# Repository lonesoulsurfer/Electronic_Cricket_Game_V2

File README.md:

# Electronic Cricket Game V2

This is a handheld electronic cricket game. Score as many runs as possible before you are out. It is a good project to learn to solder.

## Build guide and video

- Step-by-step build guide on Instructables: [Electronic Cricket Game V2](https://www.instructables.com/Electronic-Cricket-Game-V2/)
- Video on YouTube: [Electronic Cricket Game](https://youtu.be/J4yHMKsFy00)

## How to play

- Score as many runs as possible before you are out.
- I usually allow 3 outs, then the game is over.
- The board shows some cricket words, to help you learn the game. The Instructables guide has a glossary and the full rules.

## What you need

- All parts are in the parts list (`Electronic Cricket - Parts List.xlsx`).
- The schematic is [Electronic Cricket Game - Schematic.pdf](Electronic%20Cricket%20Game%20-%20Schematic.pdf).
- The Gerber files for the PCB are in `Electronic Cricket Game - Gerber File.zip`. You can send them to a PCB maker.

All parts solder directly to the PCB. You do not need wires.

## Build it

The Instructables guide shows each step, with photos. In short:

1. Send the Gerber files to a PCB maker.
2. Get the parts in the parts list.
3. Solder the parts to the PCB.
4. Connect the power and test the circuit.

## Files in this repository

| Folder or file | Contents |
|----------------|----------|
| `Electronic Cricket Game - Gerber File.zip` | Gerber files for the PCB, ready to order |
| `Eagle Files/` | Eagle files for the PCB |
| `Electronic Cricket Game - Schematic.pdf` | Schematic |
| `Electronic Cricket - Parts List.xlsx` | Parts list |

## Support

Do you like this project? You can support my work on [GitHub Sponsors](https://github.com/sponsors/lonesoulsurfer).

## Licence

This project uses the [CERN Open Hardware Licence v2, Strongly Reciprocal](LICENSE) (CERN-OHL-S-2.0). Copyright (c) 2025 Marcus (lonesoulsurfer).

You can make, change and sell boards from these files. If you share or sell a changed design, you must also share the changed design files under the same licence.

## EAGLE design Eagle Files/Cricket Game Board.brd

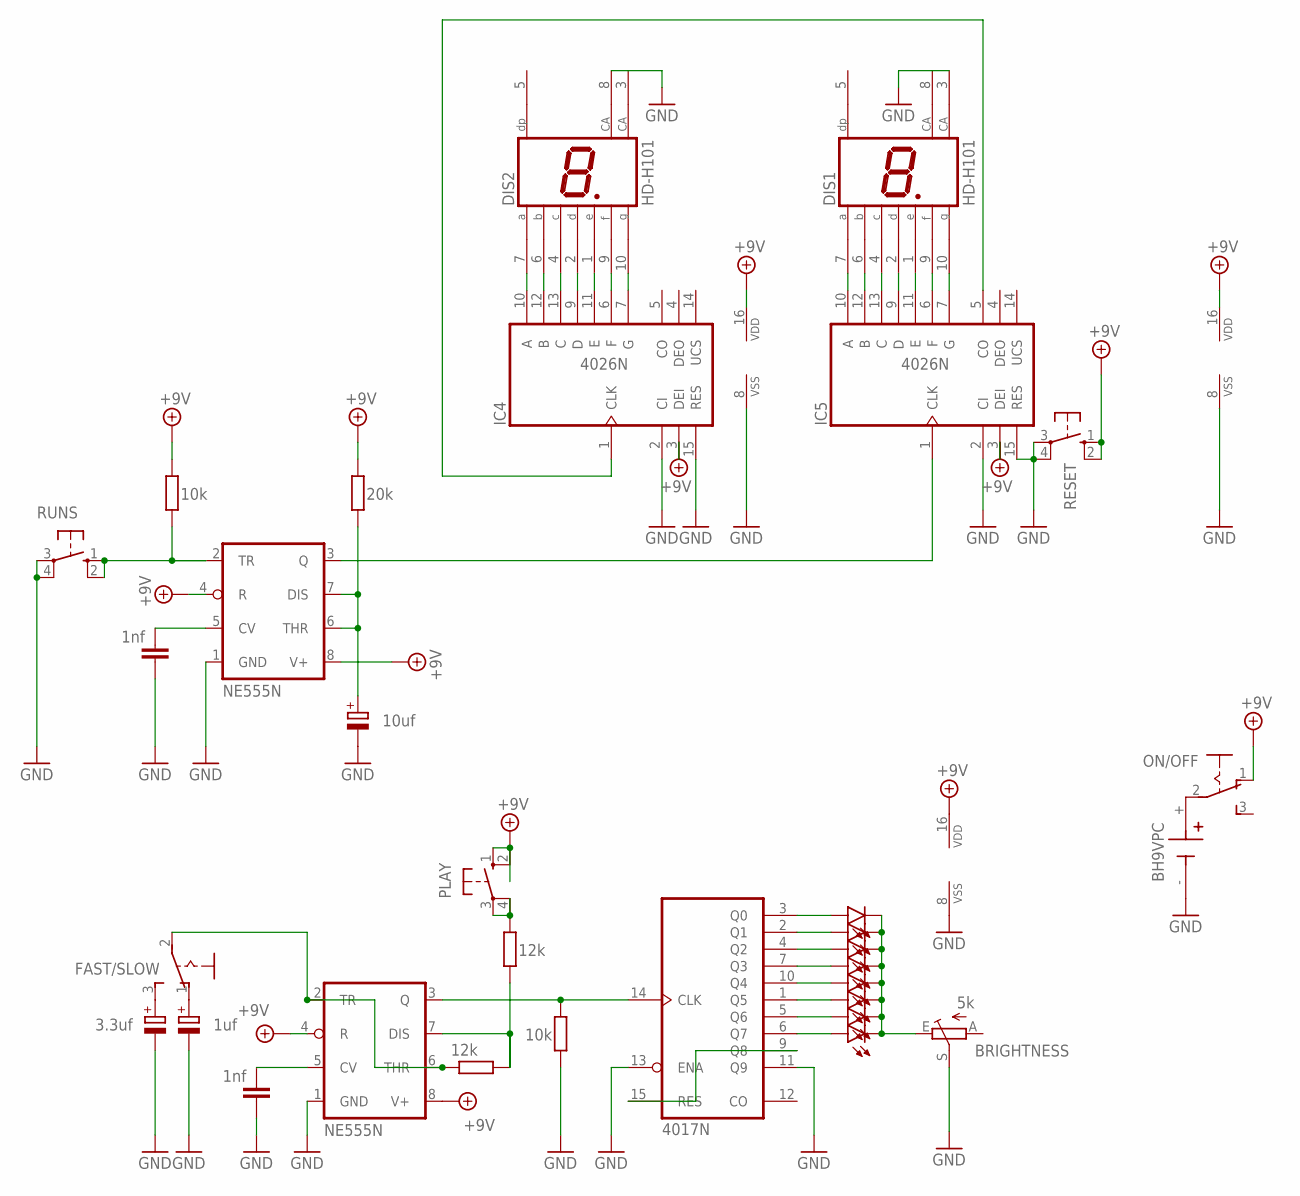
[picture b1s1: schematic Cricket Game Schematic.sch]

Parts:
BRIGHTNESS: 5k; B25P
BT1: BH9VPC; BAT_BH9VPC
C1: 1uf; E2,5-6E
C2: 3.3uf; E2,5-6E
C3, C4: 1nf; C050-024X044
C5: 10uf; E2,5-6E
DIS1, DIS2: HD-H101; HDSP-M
FAST/SLOW: M251
IC1, IC3: NE555N; DIL08
IC2: 4017N; DIL16
IC4, IC5: 4026N; DIL16
LED1, LED2, LED3, LED4, LED5, LED6, LED7, LED8: LED3MM
ON/OFF: M251
PLAY: 10-XX; B3F-10XX
R1, R2: 12k; 0207/10
R3: 20k; 0207/10
R4, R5: 10k; 0207/10
RESET: 10-XX; B3F-10XX
RUNS: 10-XX; B3F-10XX

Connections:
+9V: IC1.4 (R), IC1.8 (V+), IC2.16 (VDD), IC3.4 (R), IC3.8 (V+), IC4.3 (DEI), IC4.16 (VDD), IC5.3 (DEI), IC5.16 (VDD), ON/OFF.1 (O), PLAY.1 (S), PLAY.2 (S1), R3.1, R5.1, RESET.1 (S), RESET.2 (S1)
GND: BRIGHTNESS.S, BT1.-, C1.-, C2.-, C3.1, C4.1, C5.-, DIS1.3 (CA), DIS1.8 (CA), DIS2.3 (CA), DIS2.8 (CA), IC1.1 (GND), IC2.8 (VSS), IC2.11 (Q9), IC2.13 (ENA), IC3.1 (GND), IC4.2 (CI), IC4.8 (VSS), IC4.15 (RES), IC5.2 (CI), IC5.8 (VSS), IC5.15 (RES), R4.1, RESET.3, RESET.4 (P1), RUNS.3, RUNS.4 (P1)
unnamed: FAST/SLOW.2, IC1.2 (TR), IC1.6 (THR), R1.1
unnamed: C1.+, FAST/SLOW.1 (O)
unnamed: C2.+, FAST/SLOW.3 (S)
unnamed: IC1.7 (DIS), R1.2, R2.2
unnamed: IC1.3 (Q), IC2.14 (CLK), R4.2
unnamed: PLAY.3, PLAY.4 (P1), R2.1
unnamed: IC2.9 (Q8), IC2.15 (RES)
unnamed: IC2.3 (Q0), LED1.A
unnamed: BRIGHTNESS.E, LED1.K (C), LED2.K (C), LED3.K (C), LED4.K (C), LED5.K (C), LED6.K (C), LED7.K (C), LED8.K (C)
unnamed: IC2.2 (Q1), LED2.A
unnamed: IC2.4 (Q2), LED3.A
unnamed: IC2.7 (Q3), LED4.A
unnamed: IC2.10 (Q4), LED5.A
unnamed: IC2.1 (Q5), LED6.A
unnamed: IC2.5 (Q6), LED7.A
unnamed: IC2.6 (Q7), LED8.A
unnamed: DIS2.7 (A), IC4.10 (A)
unnamed: DIS2.6 (B), IC4.12 (B)
unnamed: DIS2.4 (C), IC4.13 (C)
unnamed: DIS2.2 (D), IC4.9 (D)
unnamed: DIS2.1 (E), IC4.11 (E)
unnamed: DIS2.9 (F), IC4.6 (F)
unnamed: DIS2.10 (G), IC4.7 (G)
unnamed: DIS1.7 (A), IC5.10 (A)
unnamed: DIS1.6 (B), IC5.12 (B)
unnamed: DIS1.4 (C), IC5.13 (C)
unnamed: DIS1.2 (D), IC5.9 (D)
unnamed: DIS1.1 (E), IC5.11 (E)
unnamed: DIS1.9 (F), IC5.6 (F)
unnamed: DIS1.10 (G), IC5.7 (G)
unnamed: IC3.3 (Q), IC5.1 (CLK)
unnamed: IC3.2 (TR), R5.2, RUNS.1 (S), RUNS.2 (S1)
unnamed: C3.2, IC1.5 (CV)
unnamed: C4.2, IC3.5 (CV)
unnamed: IC4.1 (CLK), IC5.5 (CO)
unnamed: C5.+, IC3.6 (THR), IC3.7 (DIS), R3.2
unnamed: BT1.+, ON/OFF.2

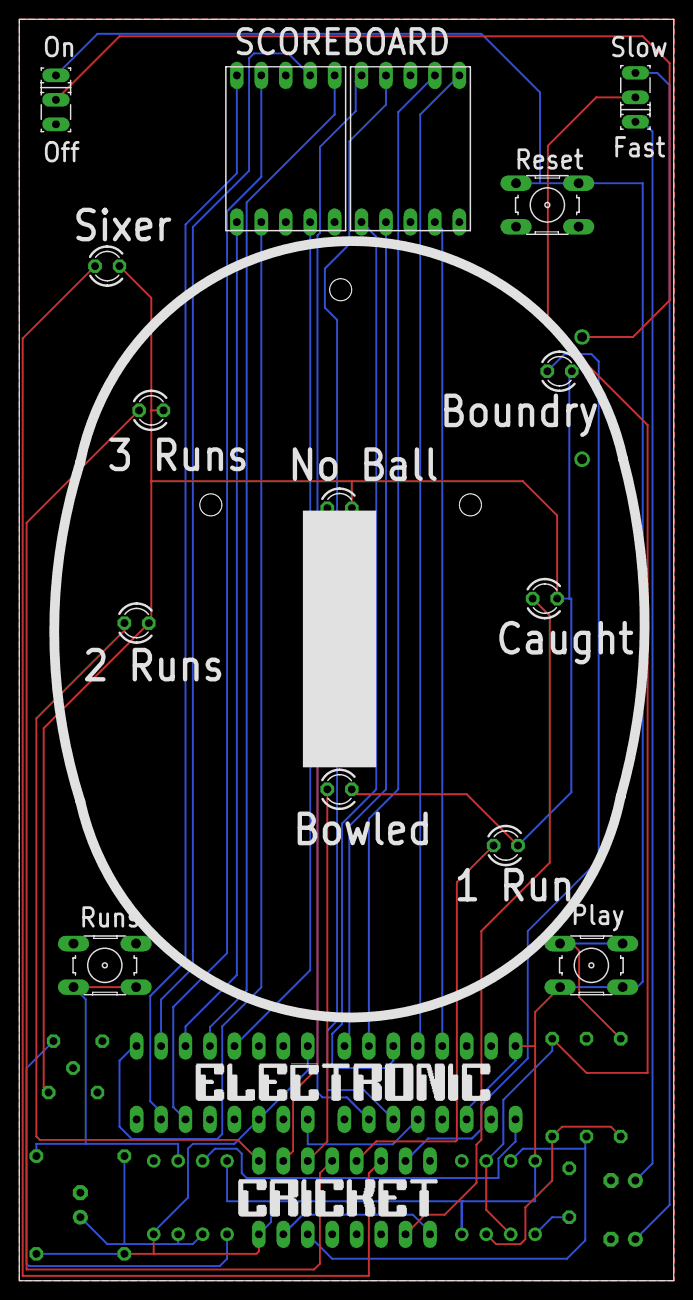
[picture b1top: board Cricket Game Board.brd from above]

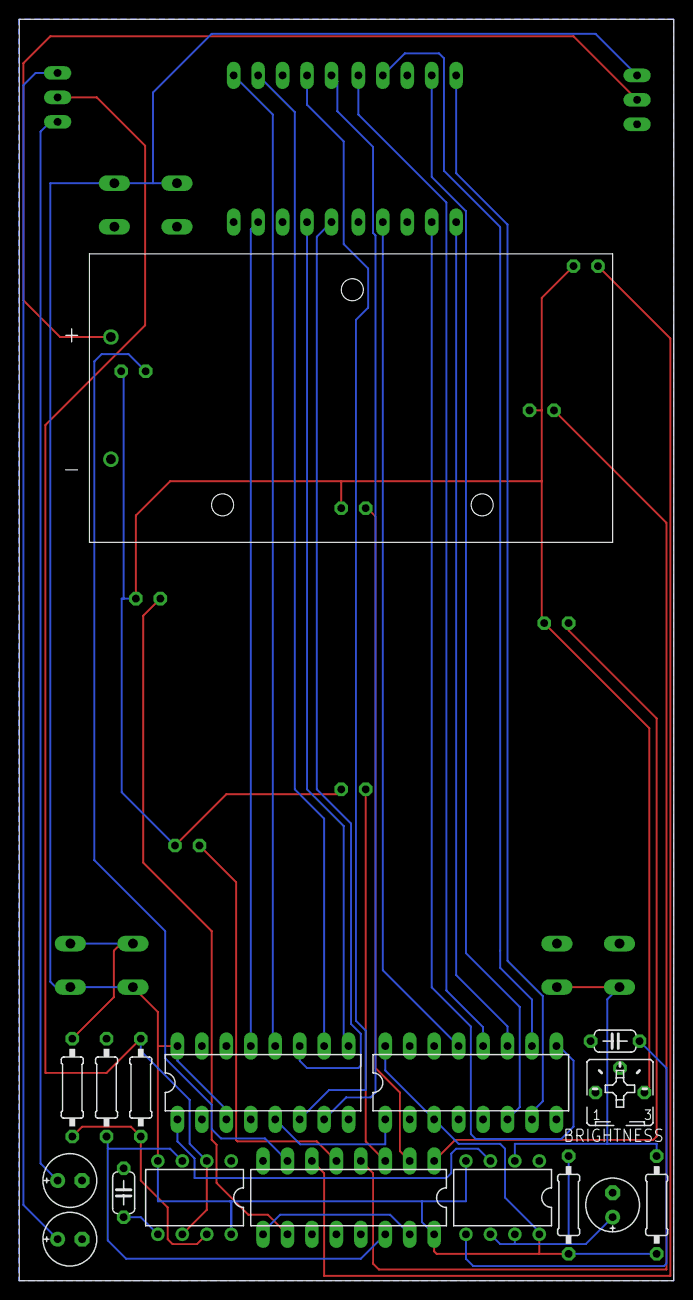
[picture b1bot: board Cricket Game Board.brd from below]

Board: 2 copper layers, 68.0 x 131.1 mm, 32 parts (17 on the bottom side), 39 nets.
